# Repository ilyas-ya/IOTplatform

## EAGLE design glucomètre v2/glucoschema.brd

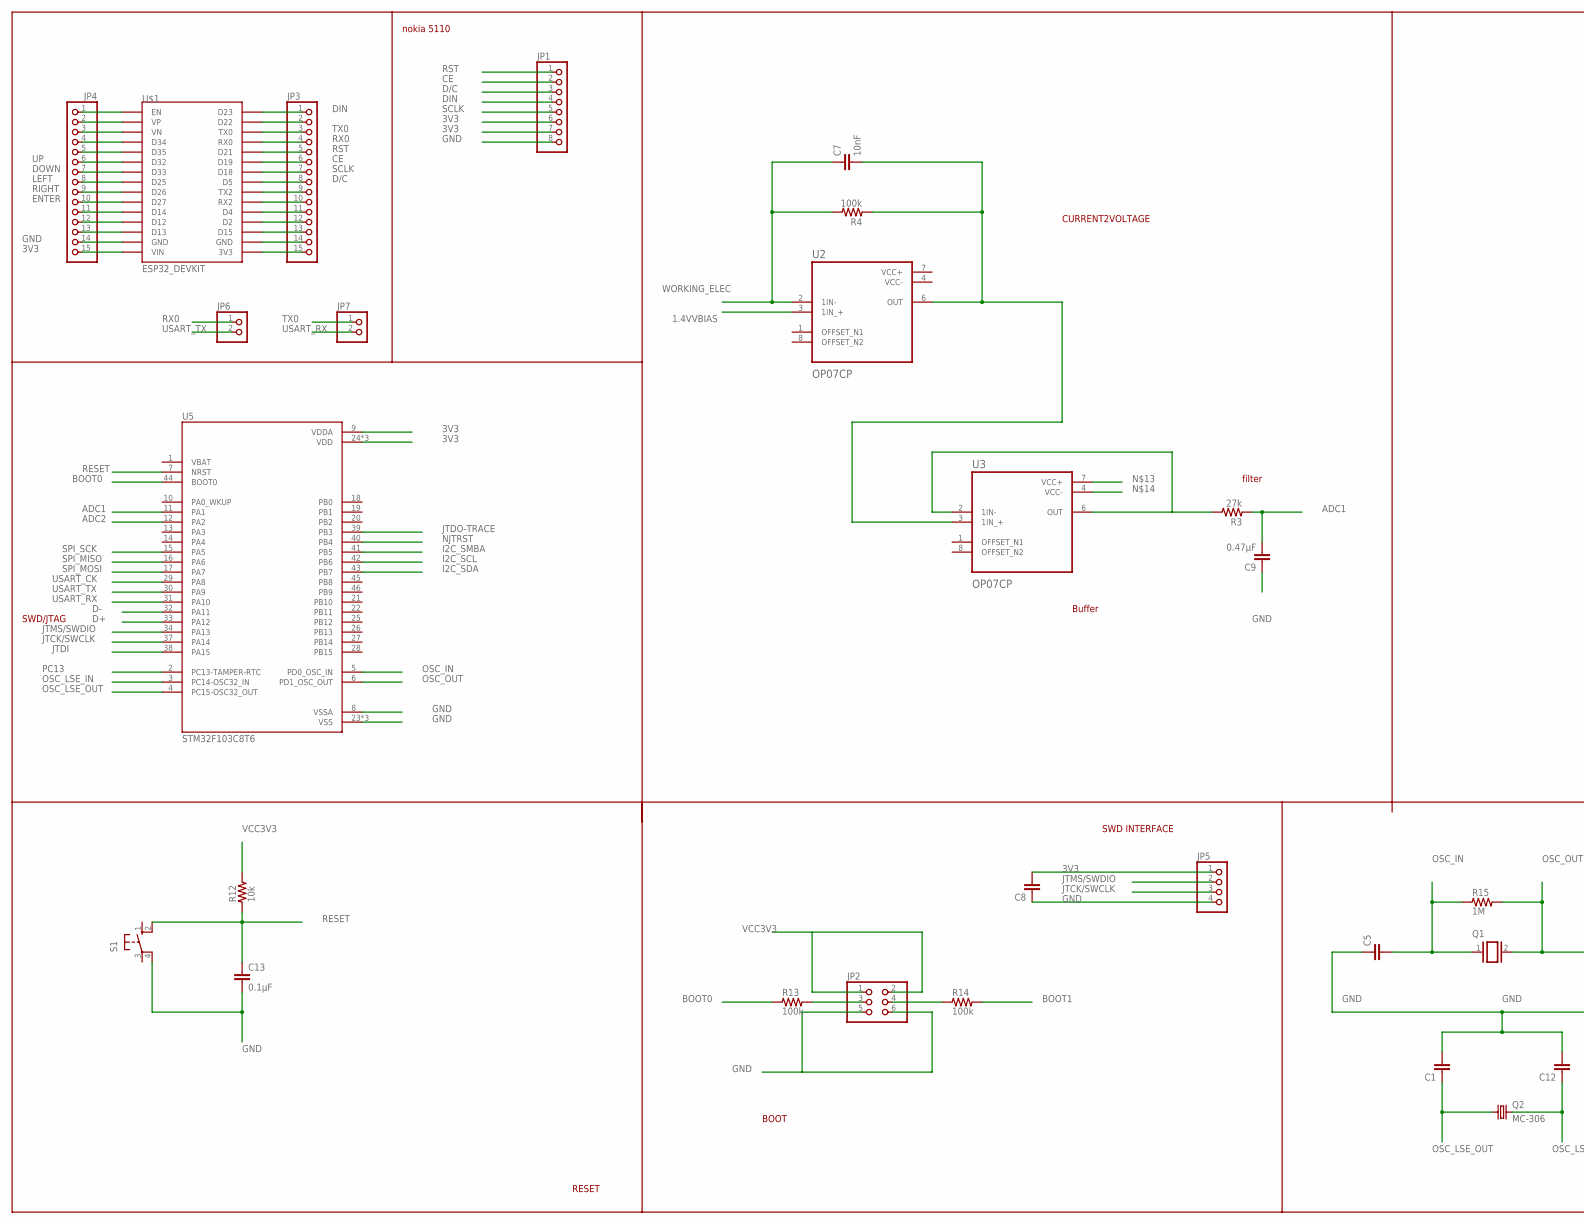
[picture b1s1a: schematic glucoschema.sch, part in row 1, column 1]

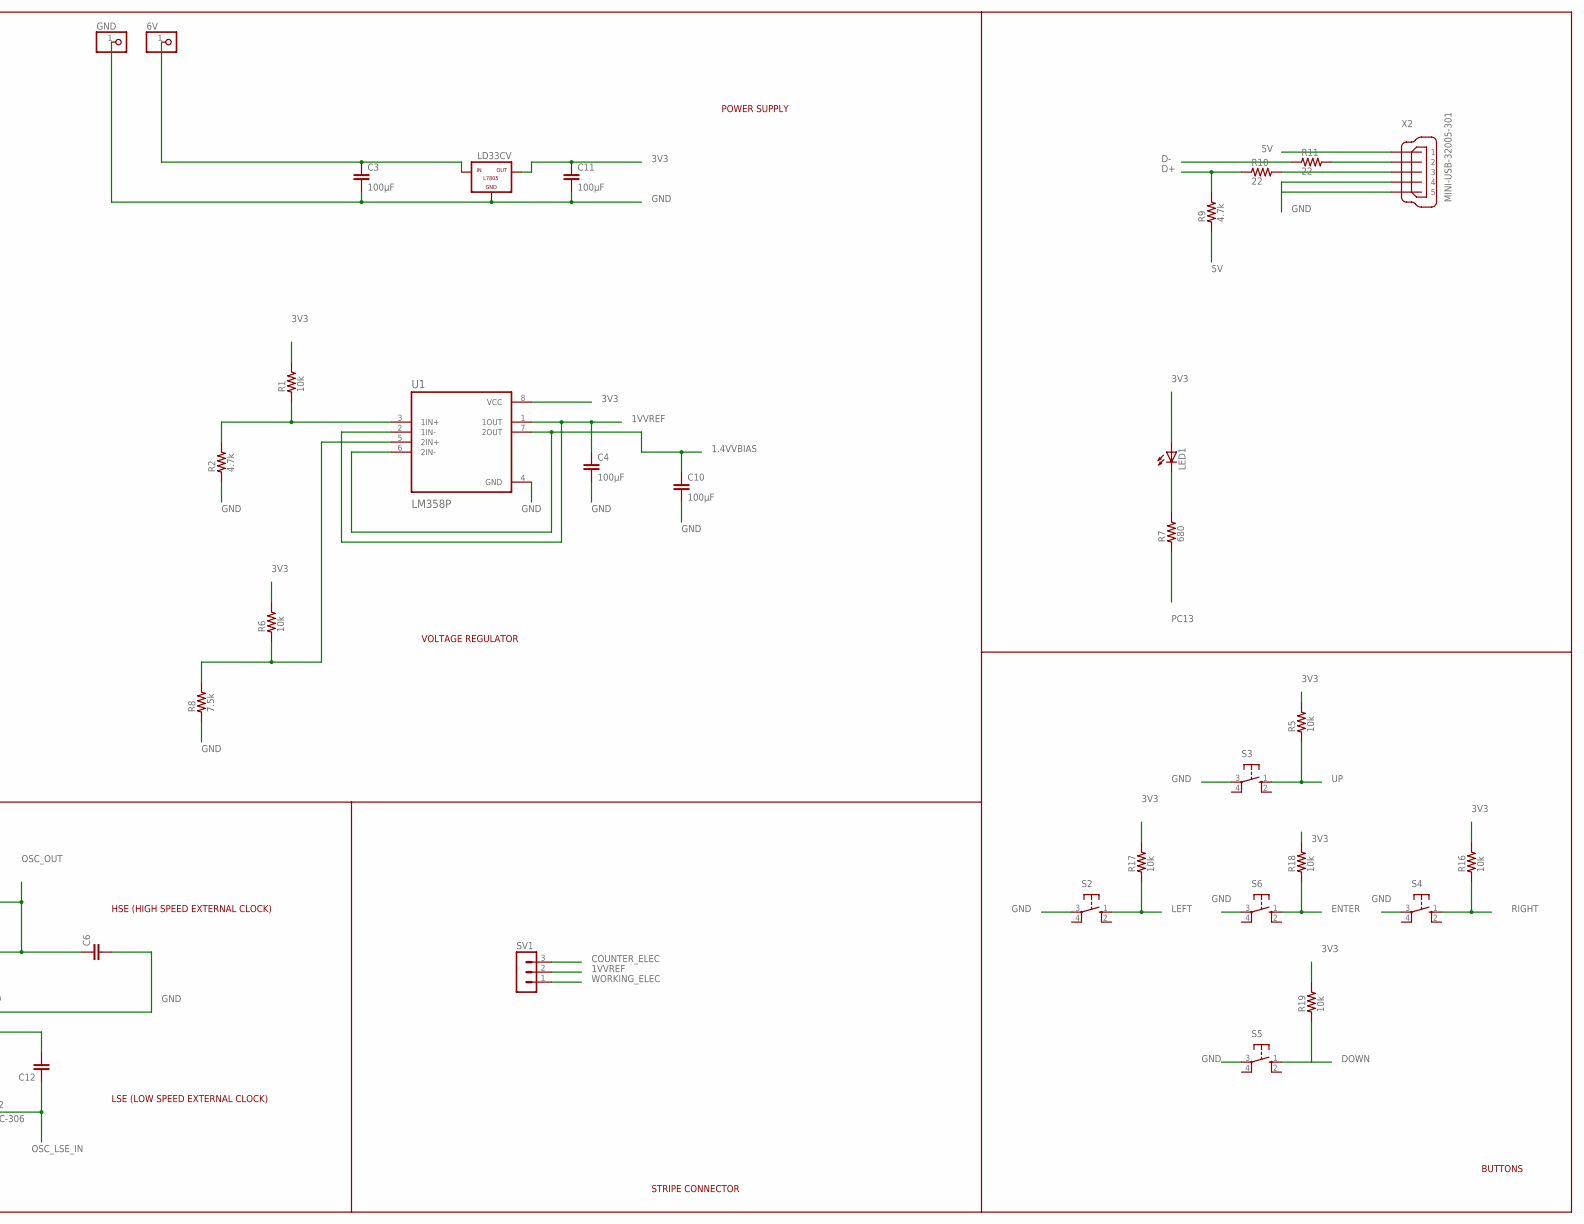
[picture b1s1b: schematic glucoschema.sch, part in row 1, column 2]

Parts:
6V: PINHD-1X1; 1X01
C1, C5, C6, C8, C12: C2.5/4; C2.5-4
C3, C4, C10, C11: 100μF; C2.5-4
C7: 10nF; C2.5-4
C9: 0.47μF; C2.5-4
C13: 0.1μF; C2.5-4
GND: PINHD-1X1; 1X01
JP1: PINHD-1X8; 1X08
JP2: PINHD-2X3; 2X03
JP3, JP4: PINHD-1X15; 1X15
JP5: PINHD-1X4; 1X04
JP6, JP7: PINHD-1X2; 1X02
LD33CV: -L7805; L7805
LED1: LED_E; LED_1206
Q1: XTAL/S; QS
Q2: MC-306
R1, R5, R6, R12, R16, R17, R18, R19: 10k; R0805
R2, R9: 4.7k; R0805
R3: 27k; R0805
R4, R13, R14: 100k; R0805
R7: 680; R0805
R8: 7.5k; R0805
R10, R11: 22; R0805
R15: 1M; R0805
S1, S2, S3, S4, S5, S6: 10-XX; B3F-10XX
SV1: MA03-1
U1: LM358P; DIP794W45P254L959H508Q8
U2, U3: OP07CP; DIP794W45P254L959H508Q8
U5: STM32F103C8T6; QFP50P900X900X160-48N
U$1: ESP32_DEVKIT
X2: MINI-USB-32005-301; 32005-301

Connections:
1.4VVBIAS: C10.1, U1.6 (2IN-), U1.7 (2OUT), U2.3 (1IN_+)
1VVREF: C4.1, SV1.2, U1.1 (1OUT), U1.2 (1IN-)
3V1: LED1.C, R7.2
3V3: C8.2, C11.1, JP1.6, JP1.7, JP4.15, JP5.1, LD33CV.OUT, LED1.A, R1.2, R5.2, R6.2, R16.2, R17.2, R18.2, R19.2, U1.8 (VCC), U5.9 (VDDA), U5.24 (VDD), U5.36 (VDD), U5.48 (VDD), U$1.VIN
5V: R9.1, X2.1
ADC1: C9.2, R3.1, U5.11 (PA1)
ADC2: U5.12 (PA2)
BOOT0: R13.1, U5.44 (BOOT0)
BOOT1: R14.2
CE: JP1.2, JP3.6, U$1.D19
COUNTER_ELEC: SV1.3
D+: R9.2, R10.1, U5.33 (PA12)
D-: R11.1, U5.32 (PA11)
D/C: JP1.3, JP3.8, U$1.D5
DIN: JP1.4, JP3.1, U$1.D23
DOWN: JP4.7, R19.1, S5.1 (S), U$1.D33
ENTER: JP4.10, R18.1, S6.1 (S), U$1.D27
GND: C1.2, C3.2, C4.2, C5.1, C6.2, C8.1, C9.1, C10.2, C11.2, C12.2, C13.2, GND.1, JP1.8, JP2.6, JP4.14, JP5.4, LD33CV.GND, R2.1, R8.1, S1.4 (P1), S2.3, S3.3, S4.3, S5.3, S6.3, U1.4 (GND), U5.8 (VSSA), U5.23 (VSS), U5.35 (VSS), U5.47 (VSS), U$1.GND@1 (GND), X2.4
I2C_SCL: U5.42 (PB6)
I2C_SDA: U5.43 (PB7)
I2C_SMBA: U5.41 (PB5)
JTCK/SWCLK: JP5.3, U5.37 (PA14)
JTDI: U5.38 (PA15)
JTDO-TRACE: U5.39 (PB3)
JTMS/SWDIO: JP5.2, U5.34 (PA13)
LEFT: JP4.8, R17.1, S2.1 (S), U$1.D25
unnamed: R1.1, R2.2, U1.3 (1IN+)
unnamed: JP2.3, R13.2
unnamed: JP2.4, R14.1
unnamed: R6.1, R8.2, U1.5 (2IN+)
unnamed: JP4.13, U$1.D13
unnamed: C7.2, R4.1, U2.6 (OUT), U3.3 (1IN_+)
unnamed: JP4.12, U$1.D12
unnamed: JP4.11, U$1.D14
unnamed: JP4.5, U$1.D35
unnamed: JP4.4, U$1.D34
unnamed: JP4.3, U$1.VN
unnamed: JP4.2, U$1.VP
unnamed: JP4.1, U$1.EN
unnamed: JP3.9, U$1.TX2
unnamed: JP3.10, U$1.RX2
unnamed: JP3.11, U$1.D4
unnamed: JP3.12, U$1.D2
unnamed: JP3.13, U$1.D15
unnamed: JP3.14, U$1.GND@2 (GND)
unnamed: JP3.15, U$1.3V3
unnamed: R11.2, X2.2
unnamed: R10.2, X2.3
unnamed: 6V.1, C3.1, LD33CV.IN
unnamed: R3.2, U3.2 (1IN-), U3.6 (OUT)
NJTRST: U5.40 (PB4)
OSC_IN: C5.2, Q1.1, R15.1, U5.5 (PD0_OSC_IN)
OSC_LSE_IN: C12.1, Q2.4 (2), U5.3 (PC14-OSC32_IN)
OSC_LSE_OUT: C1.1, Q2.1, U5.4 (PC15-OSC32_OUT)
OSC_OUT: C6.1, Q1.2, R15.2, U5.6 (PD1_OSC_OUT)
PC13: R7.1, U5.2 (PC13-TAMPER-RTC)
RESET: C13.1, R12.1, S1.2 (S1), U5.7 (NRST)
RIGHT: JP4.9, R16.1, S4.1 (S), U$1.D26
RST: JP1.1, JP3.5, U$1.D21
RX0: JP3.4, JP6.1, U$1.RX0
SCL: JP3.2, U$1.D22
SCLK: JP1.5, JP3.7, U$1.D18
SPI_MISO: U5.16 (PA6)
SPI_MOSI: U5.17 (PA7)
SPI_SCK: U5.15 (PA5)
TX0: JP3.3, JP7.1, U$1.TX0
UP: JP4.6, R5.1, S3.1 (S), U$1.D32
USART_CK: U5.29 (PA8)
USART_RX: JP7.2, U5.31 (PA10)
USART_TX: JP6.2, U5.30 (PA9)
VCC3V3: JP2.2, R12.2
VCC+: U2.7 (VCC+)
VCC-: U2.4 (VCC-)
WORKING_ELEC: C7.1, R4.2, SV1.1, U2.2 (1IN-)

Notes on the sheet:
VOLTAGE REGULATOR
SWD/JTAG
POWER SUPPLY
RESET
BOOT
HSE (HIGH SPEED EXTERNAL CLOCK)
CURRENT2VOLTAGE
STRIPE CONNECTOR
Buffer
filter
SWD INTERFACE
LSE (LOW SPEED EXTERNAL CLOCK)
BUTTONS
nokia 5110

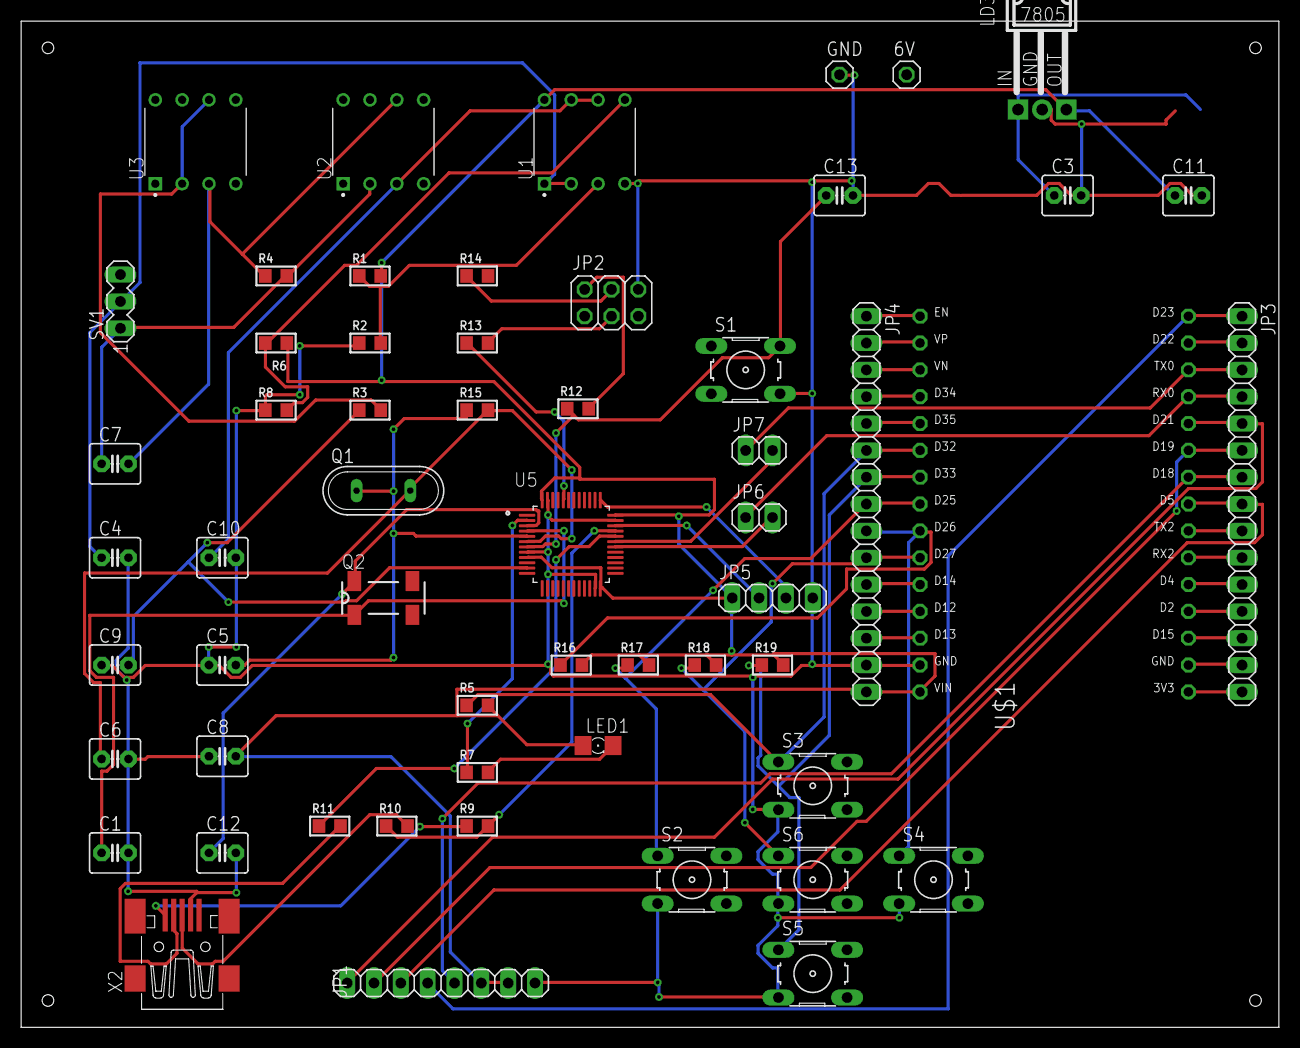
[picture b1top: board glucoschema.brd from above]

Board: 2 copper layers, 119.0 x 95.2 mm, 57 parts (0 on the bottom side), 59 nets.

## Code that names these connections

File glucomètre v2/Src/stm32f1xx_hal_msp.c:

/* USER CODE BEGIN Header */
/**
  ******************************************************************************
  * File Name          : stm32f1xx_hal_msp.c
  * Description        : This file provides code for the MSP Initialization 
  *                      and de-Initialization codes.
  ******************************************************************************
  * @attention
  *
  * <h2><center>&copy; Copyright (c) 2020 STMicroelectronics.
  * All rights reserved.</center></h2>
  *
  * This software component is licensed by ST under BSD 3-Clause license,
  * the "License"; You may not use this file except in compliance with the
  * License. You may obtain a copy of the License at:
  *                        opensource.org/licenses/BSD-3-Clause
  *
  ******************************************************************************
  */
/* USER CODE END Header */

/* Includes ------------------------------------------------------------------*/
#include "main.h"
/* USER CODE BEGIN Includes */

/* USER CODE END Includes */

/* Private typedef -----------------------------------------------------------*/
/* USER CODE BEGIN TD */

/* USER CODE END TD */

/* Private define ------------------------------------------------------------*/
/* USER CODE BEGIN Define */
 
/* USER CODE END Define */

/* Private macro -------------------------------------------------------------*/
/* USER CODE BEGIN Macro */

/* USER CODE END Macro */

/* Private variables ---------------------------------------------------------*/
/* USER CODE BEGIN PV */

/* USER CODE END PV */

/* Private function prototypes -----------------------------------------------*/
/* USER CODE BEGIN PFP */

/* USER CODE END PFP */

/* External functions --------------------------------------------------------*/
/* USER CODE BEGIN ExternalFunctions */

/* USER CODE END ExternalFunctions */

/* USER CODE BEGIN 0 */

/* USER CODE END 0 */
/**
  * Initializes the Global MSP.
  */
void HAL_MspInit(void)
{
  /* USER CODE BEGIN MspInit 0 */

  /* USER CODE END MspInit 0 */

  __HAL_RCC_AFIO_CLK_ENABLE();
  __HAL_RCC_PWR_CLK_ENABLE();

  /* System interrupt init*/

  /** DISABLE: JTAG-DP Disabled and SW-DP Disabled 
  */
  __HAL_AFIO_REMAP_SWJ_DISABLE();

  /* USER CODE BEGIN MspInit 1 */

  /* USER CODE END MspInit 1 */
}

/**
* @brief ADC MSP Initialization
* This function configures the hardware resources used in this example
* @param hadc: ADC handle pointer
* @retval None
*/
void HAL_ADC_MspInit(ADC_HandleTypeDef* hadc)
{
  GPIO_InitTypeDef GPIO_InitStruct = {0};
  if(hadc->Instance==ADC1)
  {
  /* USER CODE BEGIN ADC1_MspInit 0 */

  /* USER CODE END ADC1_MspInit 0 */
    /* Peripheral clock enable */
    __HAL_RCC_ADC1_CLK_ENABLE();
  
    __HAL_RCC_GPIOA_CLK_ENABLE();
    /**ADC1 GPIO Configuration    
    PA0-WKUP     ------> ADC1_IN0
    PA1     ------> ADC1_IN1
    PA2     ------> ADC1_IN2 
    */
    GPIO_InitStruct.Pin = GPIO_PIN_0|GPIO_PIN_1|GPIO_PIN_2;
    GPIO_InitStruct.Mode = GPIO_MODE_ANALOG;
    HAL_GPIO_Init(GPIOA, &GPIO_InitStruct);

  /* USER CODE BEGIN ADC1_MspInit 1 */

  /* USER CODE END ADC1_MspInit 1 */
  }

}

/**
* @brief ADC MSP De-Initialization
* This function freeze the hardware resources used in this example
* @param hadc: ADC handle pointer
* @retval None
*/
void HAL_ADC_MspDeInit(ADC_HandleTypeDef* hadc)
{
  if(hadc->Instance==ADC1)
  {
  /* USER CODE BEGIN ADC1_MspDeInit 0 */

  /* USER CODE END ADC1_MspDeInit 0 */
    /* Peripheral clock disable */
    __HAL_RCC_ADC1_CLK_DISABLE();
  
    /**ADC1 GPIO Configuration    
    PA0-WKUP     ------> ADC1_IN0
    PA1     ------> ADC1_IN1
    PA2     ------> ADC1_IN2 
    */
    HAL_GPIO_DeInit(GPIOA, GPIO_PIN_0|GPIO_PIN_1|GPIO_PIN_2);

  /* USER CODE BEGIN ADC1_MspDeInit 1 */

  /* USER CODE END ADC1_MspDeInit 1 */
  }

}

/**
* @brief USART MSP Initialization
* This function configures the hardware resources used in this example
* @param husart: USART handle pointer
* @retval None
*/
void HAL_USART_MspInit(USART_HandleTypeDef* husart)
{
  GPIO_InitTypeDef GPIO_InitStruct = {0};
  if(husart->Instance==USART1)
  {
  /* USER CODE BEGIN USART1_MspInit 0 */

  /* USER CODE END USART1_MspInit 0 */
    /* Peripheral clock enable */
    __HAL_RCC_USART1_CLK_ENABLE();
  
    __HAL_RCC_GPIOA_CLK_ENABLE();
    /**USART1 GPIO Configuration    
    PA8     ------> USART1_CK
    PA9     ------> USART1_TX
    PA10     ------> USART1_RX
    PA11     ------> USART1_CTS
    PA12     ------> USART1_RTS 
    */
    GPIO_InitStruct.Pin = GPIO_PIN_8|GPIO_PIN_9|GPIO_PIN_12;
    GPIO_InitStruct.Mode = GPIO_MODE_AF_PP;
    GPIO_InitStruct.Speed = GPIO_SPEED_FREQ_HIGH;
    HAL_GPIO_Init(GPIOA, &GPIO_InitStruct);

    GPIO_InitStruct.Pin = GPIO_PIN_10|GPIO_PIN_11;
    GPIO_InitStruct.Mode = GPIO_MODE_INPUT;
    GPIO_InitStruct.Pull = GPIO_NOPULL;
    HAL_GPIO_Init(GPIOA, &GPIO_InitStruct);

  /* USER CODE BEGIN USART1_MspInit 1 */

  /* USER CODE END USART1_MspInit 1 */
  }

}

/**
* @brief USART MSP De-Initialization
* This function freeze the hardware resources used in this example
* @param husart: USART handle pointer
* @retval None
*/
void HAL_USART_MspDeInit(USART_HandleTypeDef* husart)
{
  if(husart->Instance==USART1)
  {
  /* USER CODE BEGIN USART1_MspDeInit 0 */

  /* USER CODE END USART1_MspDeInit 0 */
    /* Peripheral clock disable */
    __HAL_RCC_USART1_CLK_DISABLE();
  
    /**USART1 GPIO Configuration    
    PA8     ------> USART1_CK
    PA9     ------> USART1_TX
    PA10     ------> USART1_RX
    PA11     ------> USART1_CTS
    PA12     ------> USART1_RTS 
    */
    HAL_GPIO_DeInit(GPIOA, GPIO_PIN_8|GPIO_PIN_9|GPIO_PIN_10|GPIO_PIN_11 
                          |GPIO_PIN_12);

  /* USER CODE BEGIN USART1_MspDeInit 1 */

  /* USER CODE END USART1_MspDeInit 1 */
  }

}

/* USER CODE BEGIN 1 */

/* USER CODE END 1 */

/************************ (C) COPYRIGHT STMicroelectronics *****END OF FILE****/

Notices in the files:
parts and their libraries:
rc-master-smd: Copyright (C) 2007, Bob Starr
